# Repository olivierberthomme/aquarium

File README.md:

# Aquarium
ESP8266 linked to Domoticz.

# Sensors: 
## Temperature: NTC Thermistor
https://www.aliexpress.com/item/32830765468.html
It can measure the temperature directly in the water.  It is widely used in temperature monitoring for indoor, outdoor, greenhouse, etc. You can plug the sensor onto the adapter module directory with screwing.

Specifications:
- Working voltage: 2.2~12V DC
- Working current: 0.5mA (max)
- Measuring range: -30~120℃
- Measuring Accuracy: ±2% (4℃~50℃), ±3% (-15℃~80℃)
- B value: 3950K
- R25: 10Kohm
- Sampling resistor parameters: 10k ohm, 0.1%, 10ppm
- Sensor connector: XH2.54-2P
- Lead length: 1m
- Adapter output connector: standard electronic brick interface, 2.54mm-3P header

# Domoticz integration
At startup, will query Domoticz API **by plan** and browse devices where plan matching ESP8266 hostname.
In get_DevicesIdx function, save devices indexes.

Functions send_**** will send values to Domoticz device.

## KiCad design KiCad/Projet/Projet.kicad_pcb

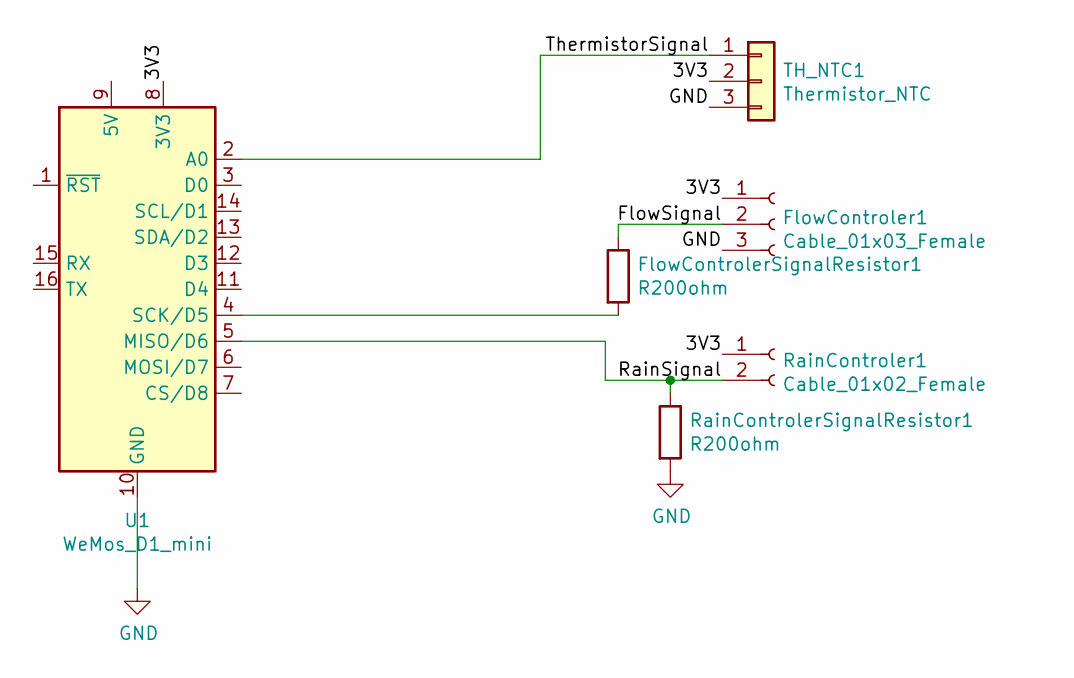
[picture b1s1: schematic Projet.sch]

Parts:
FlowControler1: Cable_01x03_Female; SolderWire-0.25sqmm_1x03_P4.2mm_D0.65mm_OD1.7mm
FlowControlerSignalResistor1: R200ohm; R_Axial_DIN0204_L3.6mm_D1.6mm_P7.62mm_Horizontal
RainControler1: Cable_01x02_Female; SolderWire-0.25sqmm_1x02_P4.5mm_D0.65mm_OD2mm
RainControlerSignalResistor1: R200ohm; R_Axial_DIN0204_L3.6mm_D1.6mm_P7.62mm_Horizontal
TH_NTC1: Thermistor_NTC; PinHeader_1x03_P1.00mm_Horizontal
U1: WeMos_D1_mini; WEMOS_D1_mini_light

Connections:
/3V3: FlowControler1.1, RainControler1.1, TH_NTC1.2, U1.8 (3V3)
/FlowSignal: FlowControler1.2, FlowControlerSignalResistor1.1
/RainSignal: RainControler1.2, RainControlerSignalResistor1.1, U1.5 (MISO/D6)
/ThermistorSignal: TH_NTC1.1, U1.2 (A0)
GND: FlowControler1.3, RainControlerSignalResistor1.2, TH_NTC1.3, U1.10 (GND)
unnamed: FlowControlerSignalResistor1.2, U1.4 (SCK/D5)

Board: 2 copper layers, 6 parts (0 on the bottom side), 6 nets, no tracks yet.

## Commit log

2020-09-01 1st WeMos D1 Mini OTA
2020-09-01 Execute function by timer
2020-09-01 Log to Syno syslog
2020-09-03 Get hardware from DZ
2020-09-03 Get devices from Dz by plan
2020-09-03 Send WifiSignal to DZ
2020-09-04 Working temp by direct analogRead
2020-09-06 Readme added
2020-10-16 Flow counter OK
2020-10-16 Rain counter OK
2021-01-05 Updates for Aquarium
